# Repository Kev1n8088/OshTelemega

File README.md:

# Mega3080 v1.0

The Mega3080 FCU is an evolved clone of the Altus Metrum Telemega. Using the same firmware (meaning the same sensor suite), the primary developments are:
- USB-C
- Wago style spring terminals
- Better GPS RF routing, and external GPS antenna
- Companion port with extra UART and space for potential direct Mosaic Integration
- Mag switch with "hard to disarm" feature 
- Slightly smaller (30x80mm instead of 31.25x82.55mm)
- Better reverse polarity protection, including on pyro charges
- Cheaper than purchasing a TeleMega

## Basic Manual

All Wago ports are the same as the Telemega screw terminals, except for the addition of a connector to select between an external switch and the internal mag switch (you can use both!).

To enable the internal mag switch, bridge the terminals marked **MG**. A magnet's **N** pole perpendicular to the top surface magnetic sensor (under the square buzzer) arms the device. 

A fully armed device has the dual-LED next to the mag sensor fully lit (green and red). To begin the disarm process, expose the sensor to a **S** pole, then a **N** pole, and then an **S** pole. This will cycle the LED lights. This feature prevents any risk of disarming from launch towers that may generate magnetic fields.

If a device on the pad has a partially lit LED, the disarm process has started. It is recommended that a disarm and arming cycle be completed to reduce the risk of inadvertent disarm; however, even during the disarm process, the device remains as, if not less, sensitive to stray magnetic fields as industry-standard altimeters.

To use an external switch, simply wire it in series with the terminals marked **SW**. 

If you want an external switch in parallel with the internal mag switch **(NOT RECOMMENDED)** - you can wire both a switch in series with the **SW** terminals, and bridge the **MG** terminals. 

If you want an external switch in series with the internal mag switch **(MAYBE ALRIGHT?)** - you can wire a switch in series with the **MG** terminals. 

To enable GPS operation, connect a standard L1 patch antenna to the rear UFL connector marked L1 GPS. This port supports both passive and active patch antennas. 

Companion and servo connector documentation TBD

See the `flashing.md` file for flashing info. 

## Production
All SMT components can be assembled via JLCPCB.

THT BOM is to be produced soon. 

Use the `jlcpcb/production_files` subdirectory for production files. I do not guarantee that everything will be in stock on JLC, nor do I guarantee that the rotations are correct (they are not, **CHECK VERY CAREFULLY!**).

Recommended configuration is **JLC04161H-7628**. I recommend ENIG, but it's likely not necessary. 

## Notes
Use at your own risk! This device has not been validated as of Dec 2025, and custom production from JLC always carries the risk of QC issues. 

You must provide your own patch antenna (preferably active) to use the GPS

There are a few minor issues known with the v1.0 model: 

- When powered through the mag switch, there is a diode in the path for pyro power. This shouldn't be an issue in practice, but it is technically rated only for 1A continuous. The transient rating is more than enough at 50A, so it's not really a huge issue. There is also a slight voltage drop. Not an issue when the mag switch is bypassed or when a separate pyro battery is used.
- Theoretically, the vertical USB-C Connector is more fragile than a horizontal one - and also harder to solder with a hot air station. Take care when using heavy cables, and if you are concerned, epoxy the connector down.
- Due to a technical oversight, the separate pyro battery capability of the stock telemega, which is rated up to 30v, has to be derated to 12v on the Mega3080. Not sure how many people use a 12+v external pyro battery, but something to be aware of.

The v1.1 release has fixed the USB-C issue; however, the v1.1 device has not been produced yet. Use at your own risk.  

---

**Device Version Last Produced Officially:** v1.0

**Last Updated:** December 2025  

**Written by:** Kevin Zheng (Kev1n8088)

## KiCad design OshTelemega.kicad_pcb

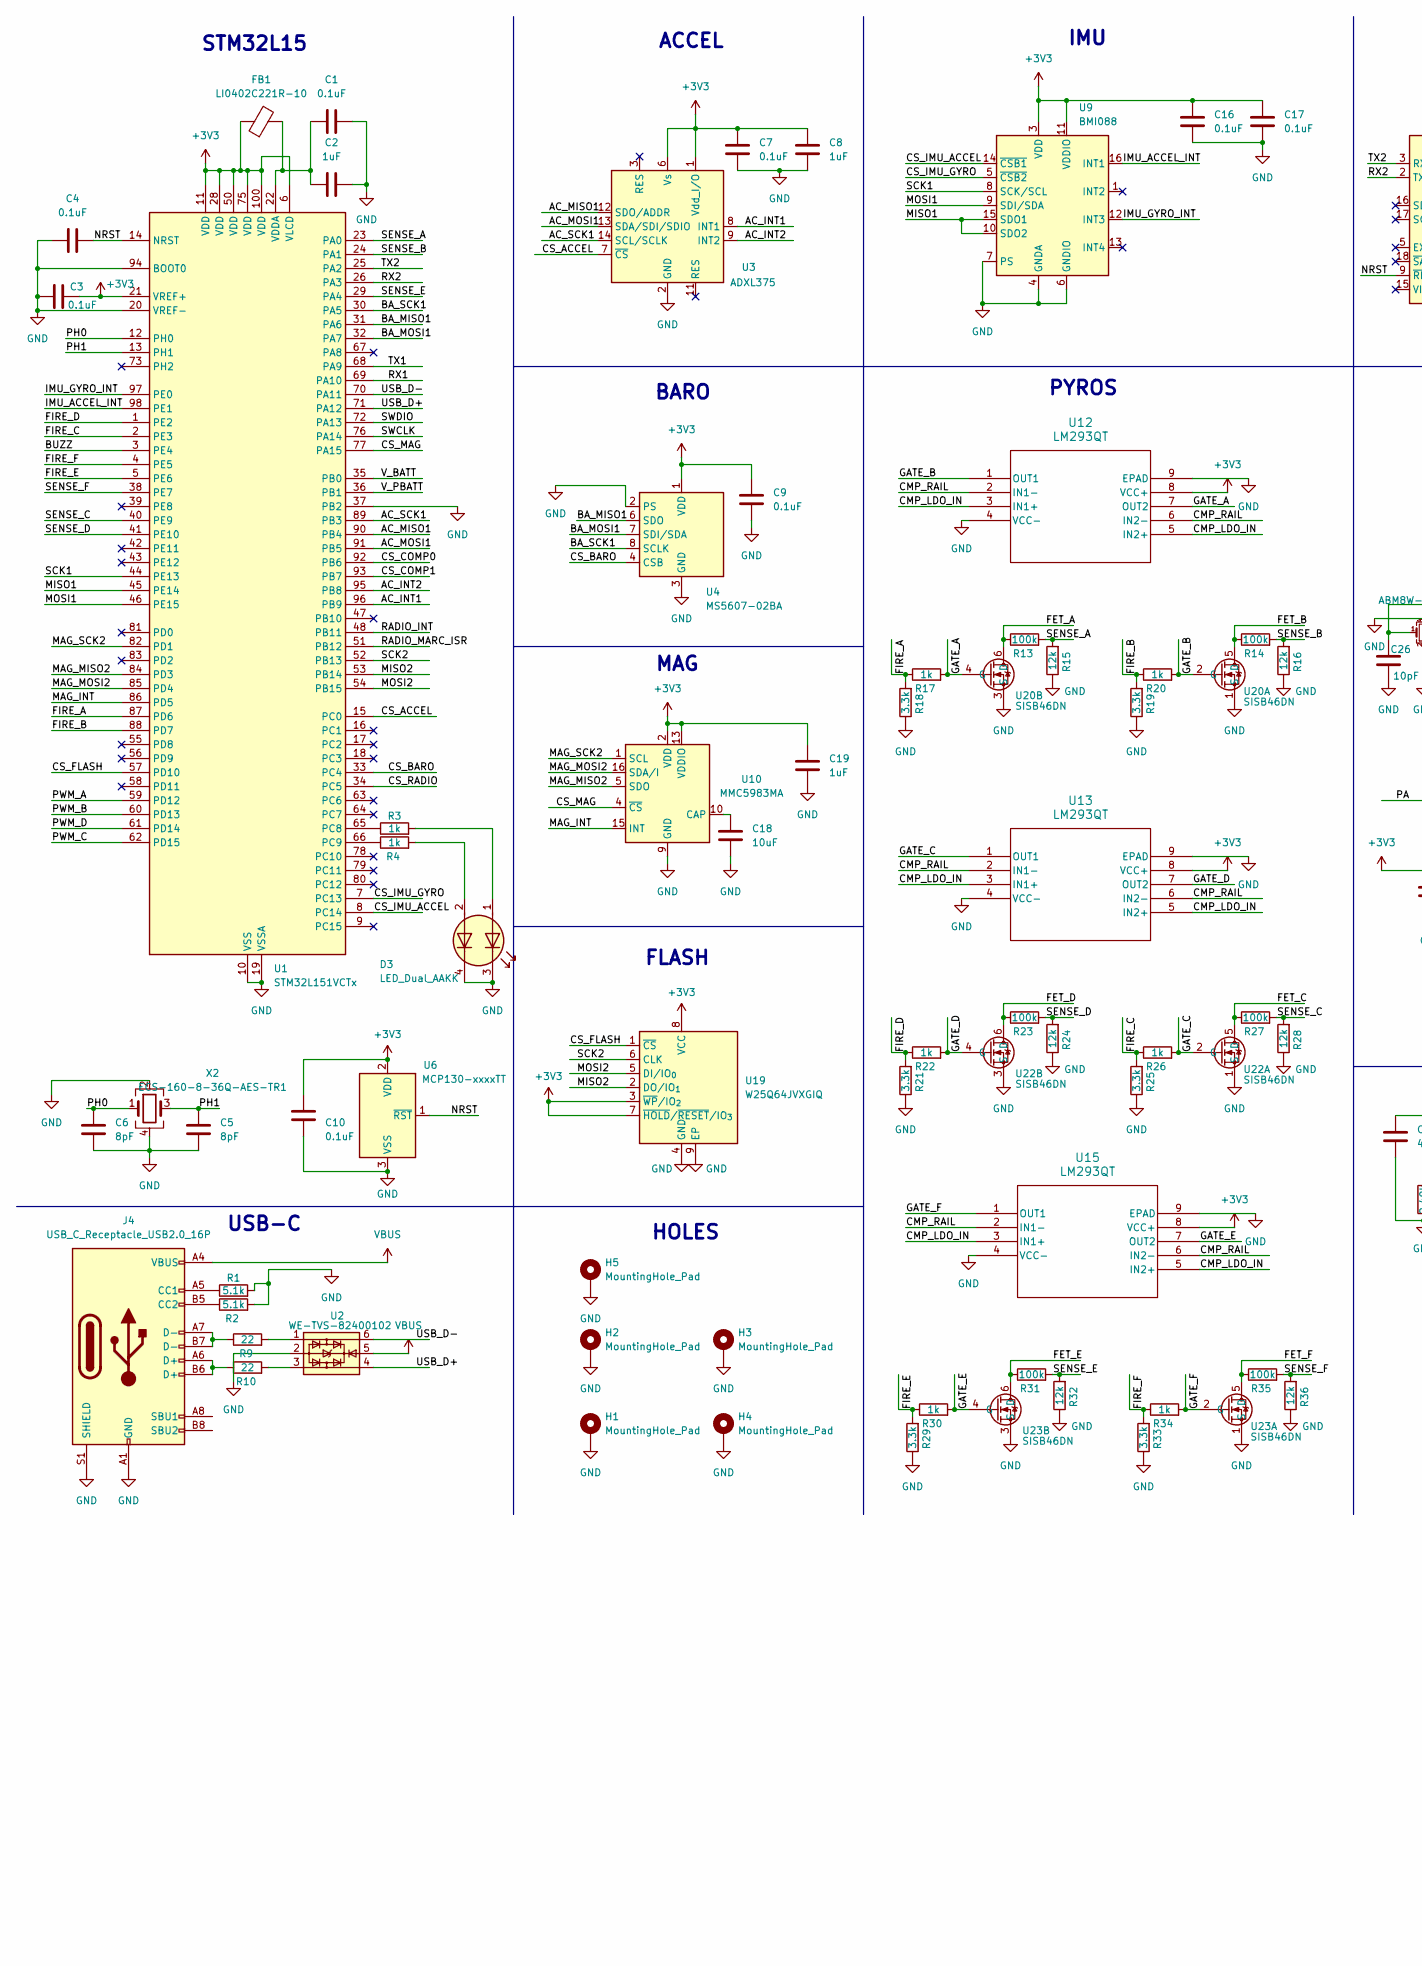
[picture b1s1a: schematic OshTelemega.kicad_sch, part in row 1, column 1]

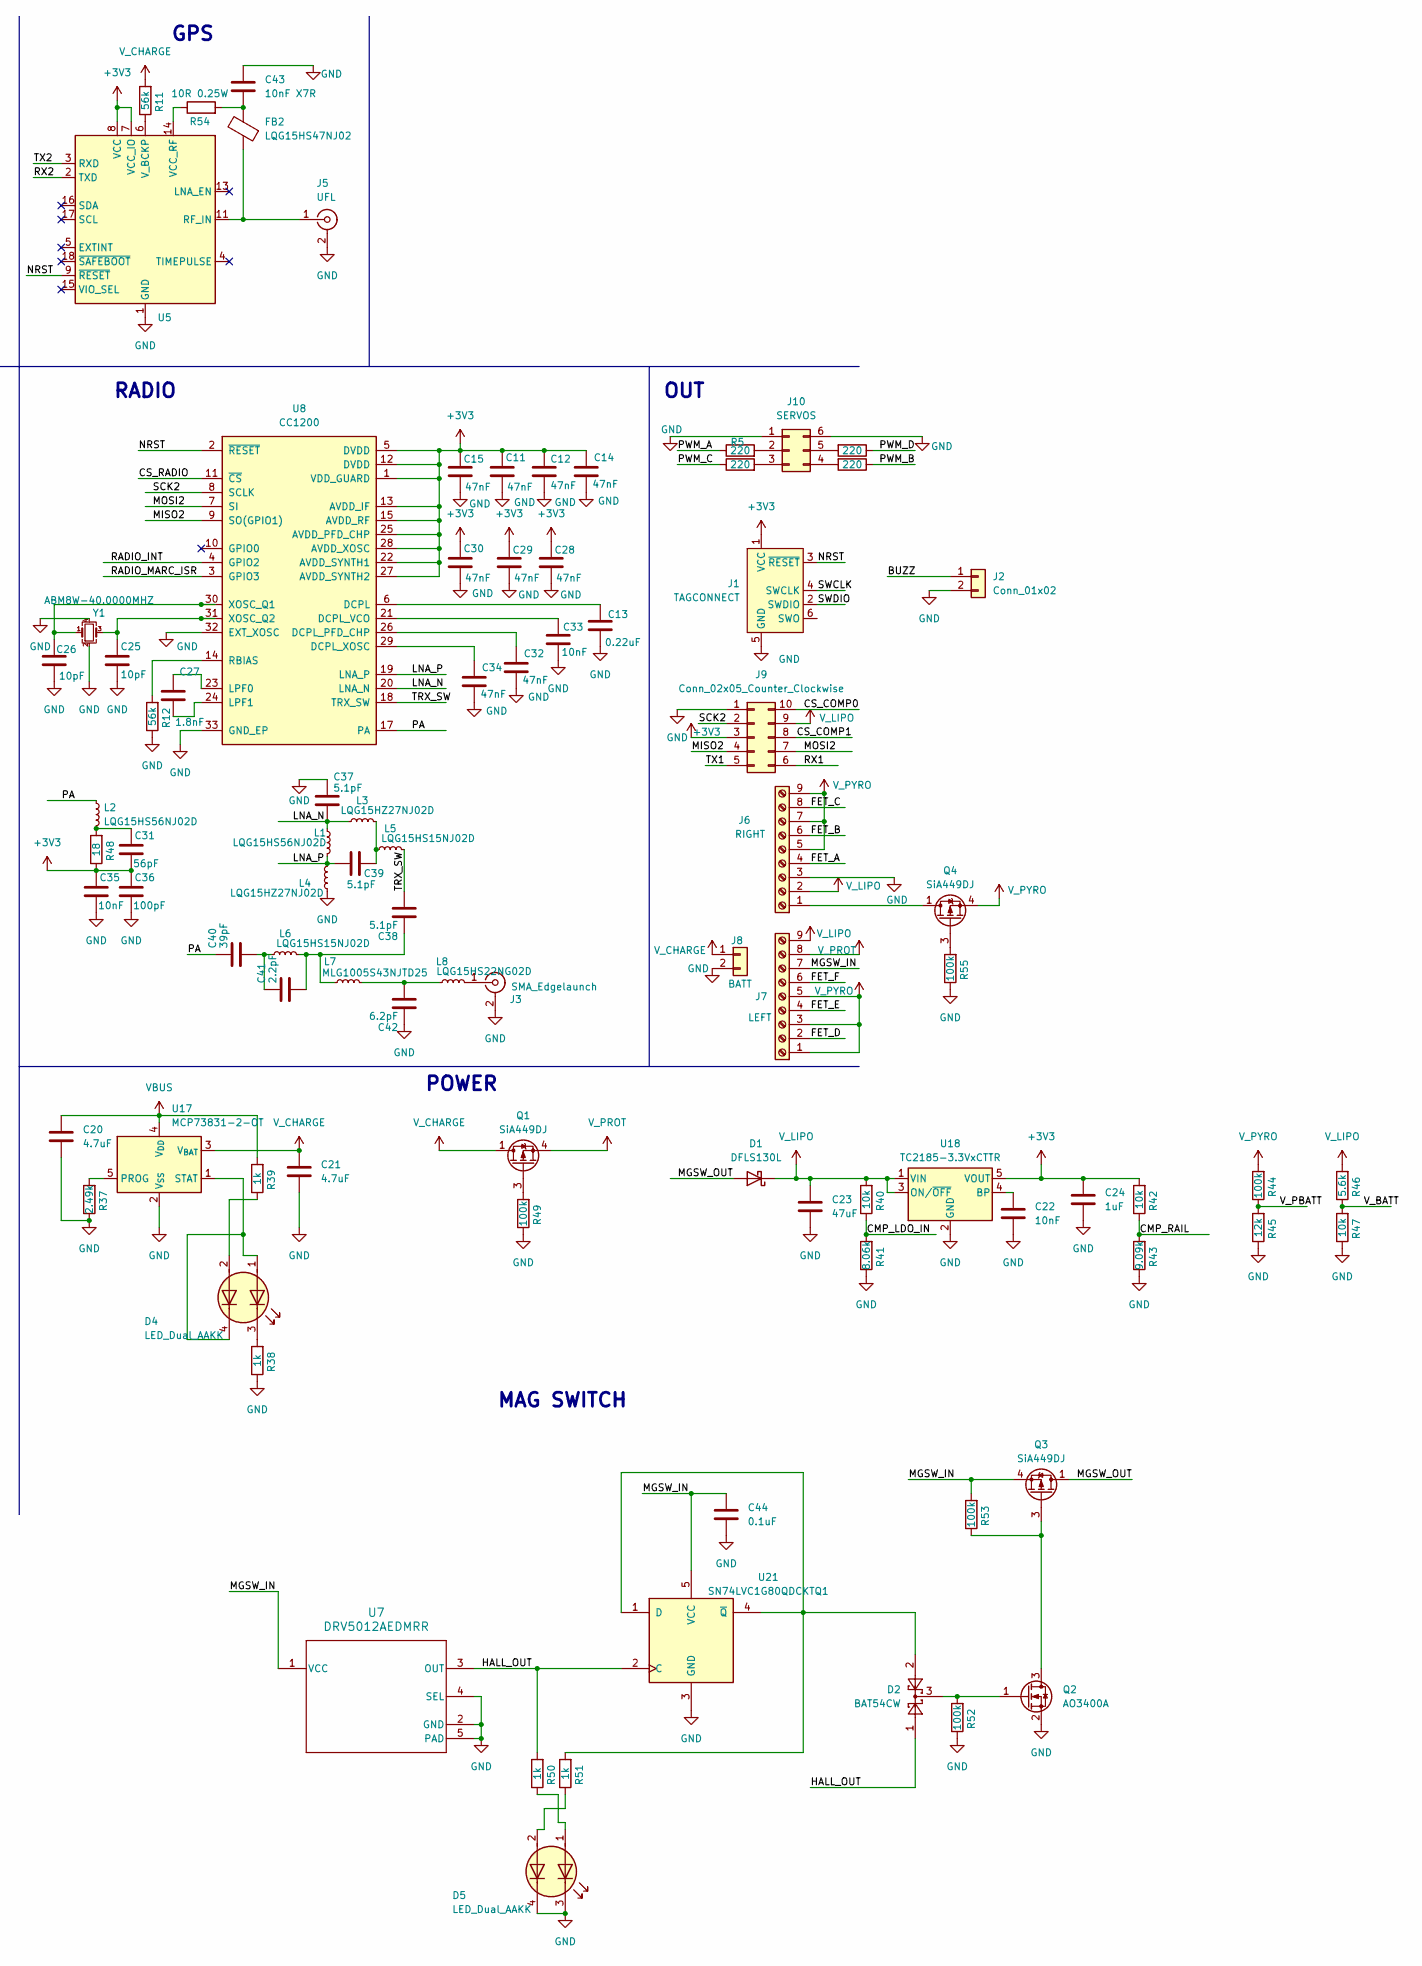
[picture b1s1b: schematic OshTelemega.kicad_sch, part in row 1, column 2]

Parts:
C1, C3, C4, C7, C9, C10, C16, C17, C44: 0.1uF; C_0402_1005Metric
C2, C8, C19, C24: 1uF; C_0402_1005Metric
C5, C6: 8pF; C_0402_1005Metric
C11, C12, C14, C15, C28, C29, C30, C32, C34: 47nF; C_0402_1005Metric
C13: 0.22uF; C_0402_1005Metric
C18: 10uF; C_0402_1005Metric
C20, C21: 4.7uF; C_0402_1005Metric
C22, C33, C35: 10nF; C_0402_1005Metric
C23: 47uF; C_1206_3216Metric
C25, C26: 10pF; C_0402_1005Metric
C27: 1.8nF; C_0402_1005Metric
C31: 56pF; C_0402_1005Metric
C36: 100pF; C_0402_1005Metric
C37, C38, C39: 5.1pF; C_0402_1005Metric
C40: 39pF; C_0402_1005Metric
C41: 2.2pF; C_0402_1005Metric
C42: 6.2pF; C_0402_1005Metric
C43: 10nF X7R; C_0402_1005Metric
D1: DFLS130L; D_PowerDI-123
D2: BAT54CW; SOT-323_SC-70
D3, D4, D5: LED_Dual_AAKK; DualLED0606
FB1: LI0402C221R-10; L_0402_1005Metric
FB2: LQG15HS47NJ02; L_0402_1005Metric
H1, H2, H3, H4, H5: MountingHole_Pad; MountingHole_3.2mm_M3_DIN965_Pad
J1: TAGCONNECT; Tag-Connect_TC2030-IDC-NL_2x03_P1.27mm_Vertical
J2: Conn_01x02; PinHeader_1x02_P1.27mm_Vertical
J3: SMA_Edgelaunch; SMA_Amphenol_132289_EdgeMount
J4: USB_C_Receptacle_USB2.0_16P; USB_C_Receptacle_G-Switch_GT-USB-7051x
J5: UFL; U.FL_Molex_MCRF_73412-0110_Vertical
J6: RIGHT; CONN9_250-309_WAG
J7: LEFT; CONN9_250-309_WAG
J8: BATT; JST_PH_B2B-PH-K_1x02_P2.00mm_Vertical
J9: Conn_02x05_Counter_Clockwise; PinHeader_2x05_P1.27mm_Vertical
J10: SERVOS; PinHeader_2x03_P1.27mm_Vertical
L1, L2: LQG15HS56NJ02D; L_0402_1005Metric
L3, L4: LQG15HZ27NJ02D; L_0402_1005Metric
L5, L6: LQG15HS15NJ02D; L_0402_1005Metric
L7: MLG1005S43NJTD25; L_0402_1005Metric
L8: LQG15HS22NG02D; L_0402_1005Metric
Q1, Q3, Q4: SiA449DJ; Vishay_PowerPAK_SC70-6L_Single
Q2: AO3400A; SOT-23
R1, R2: 5.1k; R_0402_1005Metric
R3, R4, R17, R20, R22, R26, R30, R34, R38, R39, R50, R51: 1k; R_0402_1005Metric
R5, R6, R7, R8: 220; R_0402_1005Metric
R9, R10: 22; R_0402_1005Metric
R11, R12: 56k; R_0402_1005Metric
R13, R14, R23, R27, R31, R35, R44, R49, R52, R53, R55: 100k; R_0402_1005Metric
R15, R16, R24, R28, R32, R36, R45: 12k; R_0402_1005Metric
R18, R19, R21, R25, R29, R33: 3.3k; R_0402_1005Metric
R37: 2.49k; R_0402_1005Metric
R40, R42, R47: 10k; R_0402_1005Metric
R41: 8.06k; R_0402_1005Metric
R43: 9.09k; R_0402_1005Metric
R46: 5.6k; R_0402_1005Metric
R48: 18; R_0402_1005Metric
R54: 10R 0.25W; R_0402_1005Metric
U1: STM32L151VCTx; LQFP-100_14x14mm_P0.5mm
U2: WE-TVS-82400102; SOT-23-6
U3: ADXL375; LGA-14_3x5mm_P0.8mm_LayoutBorder1x6y
U4: MS5607-02BA; LGA-8_3x5mm_P1.25mm
U5: MAX-M10S; ublox_MAX
U6: MCP130-xxxxTT; SOT-23
U7: DRV5012AEDMRR; Texas_X2SON-4-1EP_1.1x1.4mm_P0.5mm_EP0.8x0.6mm
U8: CC1200; QFN-32-1EP_5x5mm_P0.5mm_EP3.45x3.45mm
U9: BMI088; Bosch_LGA-16_4.5x3mm_P0.5mm_LayoutBorder7x1y_ClockwisePinNu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
U10: MMC5983MA; LGA-16_3x3mm_P0.5mm
U12, U13, U15: LM293QT; DFN-8-1EP_2x2mm_P0.5mm_EP0.9x1.6mm
U17: MCP73831-2-OT; SOT-23-5
U18: TC2185-3.3VxCTTR; SOT-23-5
U19: W25Q64JVXGIQ; DFN_XGIQ TR_WIN
U20, U22, U23: SISB46DN; PowerPak1212-8-Dual
U21: SN74LVC1G80QDCKTQ1; SOT-353_SC-70-5
X2: ECS-160-8-36Q-AES-TR1; Crystal_SMD_2520-4Pin_2.5x2.0mm
Y1: ABM8W-40.0000MHZ; Crystal_SMD_Abracon_ABM8G-4Pin_3.2x2.5mm

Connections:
+3V3: C3.2, C7.2, C8.2, C9.2, C10.2, C11.2, C12.2, C14.2, C15.2, C16.2, C17.2, C19.2, C24.2, C28.2, C29.2, C30.2, C31.1, C35.2, C36.2, FB1.1, J1.1 (VCC), J9.3, R42.2, R48.1, U1.6 (VLCD), U1.11 (VDD), U1.21 (VREF+), U1.28 (VDD), U1.50 (VDD), U1.75 (VDD), U1.100 (VDD), U3.1 (Vdd_I/O), U3.6 (Vs), U4.1 (VDD), U5.7 (VCC_IO), U5.8 (VCC), U6.2 (VDD), U8.1 (VDD_GUARD), U8.5 (DVDD), U8.12 (DVDD), U8.13 (AVDD_IF), U8.15 (AVDD_RF), U8.22 (AVDD_SYNTH1), U8.25 (AVDD_PFD_CHP), U8.27 (AVDD_SYNTH2), U8.28 (AVDD_XOSC), U9.3 (VDD), U9.11 (VDDIO), U10.2 (VDD), U10.13 (VDDIO), U12.8 (VCC+), U13.8 (VCC+), U15.8 (VCC+), U18.5 (VOUT), U19.3 (~WP/IO_{2}), U19.7 (~HOLD/~RESET/IO_{3}), U19.8 (VCC)
/AC_INT1: U1.96 (PB9), U3.8 (INT1)
/AC_INT2: U1.95 (PB8), U3.9 (INT2)
/AC_MISO1: U1.90 (PB4), U3.12 (SDO/ADDR)
/AC_MOSI1: U1.91 (PB5), U3.13 (SDA/SDI/SDIO)
/AC_SCK1: U1.89 (PB3), U3.14 (SCL/SCLK)
/BA_MISO1: U1.31 (PA6), U4.6 (SDO)
/BA_MOSI1: U1.32 (PA7), U4.7 (SDI/SDA)
/BA_SCK1: U1.30 (PA5), U4.8 (SCLK)
/BUZZ: J2.1, U1.3 (PE4); also elsewhere on the board
/CMP_LDO_IN: R40.1, R41.2, U12.3 (IN1+), U12.5 (IN2+), U13.3 (IN1+), U13.5 (IN2+), U15.3 (IN1+), U15.5 (IN2+)
/CMP_RAIL: R42.1, R43.2, U12.2 (IN1-), U12.6 (IN2-), U13.2 (IN1-), U13.6 (IN2-), U15.2 (IN1-), U15.6 (IN2-)
/CS_ACCEL: U1.15 (PC0), U3.7 (~CS)
/CS_BARO: U1.33 (PC4), U4.4 (CSB), U4.5 (CSB)
/CS_COMP0: J9.10, U1.92 (PB6)
/CS_COMP1: J9.8, U1.93 (PB7)
/CS_FLASH: U1.57 (PD10), U19.1 (~CS)
/CS_IMU_ACCEL: U1.8 (PC14), U9.14 (~CSB1)
/CS_IMU_GYRO: U1.7 (PC13), U9.5 (~CSB2)
/CS_MAG: U1.77 (PA15), U10.4 (~CS)
/CS_RADIO: U1.34 (PC5), U8.11 (~CS)
/FET_A: J6.4, R13.1, U20.6 (D)
/FET_B: J6.6, R14.1, U20.5 (D)
/FET_C: J6.8, R27.1, U22.5 (D)
/FET_D: J7.2, R23.1, U22.6 (D)
/FET_E: J7.4, R31.1, U23.6 (D)
/FET_F: J7.6, R35.1, U23.5 (D)
/FIRE_A: R17.1, R18.2, U1.87 (PD6)
/FIRE_B: R19.2, R20.1, U1.88 (PD7)
/FIRE_C: R25.2, R26.1, U1.2 (PE3)
/FIRE_D: R21.2, R22.1, U1.1 (PE2)
/FIRE_E: R29.2, R30.1, U1.5 (PE6)
/FIRE_F: R33.2, R34.1, U1.4 (PE5)
/GATE_A: R17.2, U12.7 (OUT2), U20.4 (G)
/GATE_B: R20.2, U12.1 (OUT1), U20.2 (G)
/GATE_C: R26.2, U13.1 (OUT1), U22.2 (G)
/GATE_D: R22.2, U13.7 (OUT2), U22.4 (G)
/GATE_E: R30.2, U15.7 (OUT2), U23.4 (G)
/GATE_F: R34.2, U15.1 (OUT1), U23.2 (G)
/HALL_OUT: D2.1, R50.2, U7.3 (OUT), U21.2 (C)
/IMU_ACCEL_INT: U1.98 (PE1), U9.16 (INT1)
/IMU_GYRO_INT: U1.97 (PE0), U9.12 (INT3)
/LNA_N: C37.1, L1.1, L3.1, U8.20 (LNA_N)
/LNA_P: C39.2, L1.2, L4.2, U8.19 (LNA_P)
/MAG_INT: U1.86 (PD5), U10.15 (INT)
/MAG_MISO2: U1.84 (PD3), U10.5 (SDO)
/MAG_MOSI2: U1.85 (PD4), U10.16 (SDA/I)
/MAG_SCK2: U1.82 (PD1), U10.1 (SCL)
/MGSW_IN: C44.2, J7.7, Q3.4 (S), R53.2, U7.1 (VCC), U21.5 (VCC)
/MGSW_OUT: D1.2 (A), Q3.1 (D)
/MISO1: U1.45 (PE14), U9.10 (SDO2), U9.15 (SDO1)
/MISO2: J9.4, U1.53 (PB14), U8.9 (SO(GPIO1)), U19.2 (DO/IO_{1})
/MOSI1: U1.46 (PE15), U9.9 (SDI/SDA)
/MOSI2: J9.7, U1.54 (PB15), U8.7 (SI), U19.5 (DI/IO_{0})
/NRST: C4.2, J1.3 (~RESET), U1.14 (NRST), U5.9 (~RESET), U6.1 (~RST), U8.2 (~RESET)
/PA: C40.2, L2.1, U8.17 (PA)
/PH0: C6.2, U1.12 (PH0), X2.1
/PH1: C5.2, U1.13 (PH1), X2.3
/PWM_A: R5.1, U1.59 (PD12)
/PWM_B: R6.1, U1.60 (PD13)
/PWM_C: R7.1, U1.62 (PD15)
/PWM_D: R8.1, U1.61 (PD14)
/RADIO_INT: U1.48 (PB11), U8.4 (GPIO2)
/RADIO_MARC_ISR: U1.51 (PB12), U8.3 (GPIO3)
/RX1: J9.6, U1.69 (PA10)
/RX2: U1.26 (PA3), U5.2 (TXD)
/SCK1: U1.44 (PE13), U9.8 (SCK/SCL)
/SCK2: J9.2, U1.52 (PB13), U8.8 (SCLK), U19.6 (CLK)
/SENSE_A: R13.2, R15.2, U1.23 (PA0)
/SENSE_B: R14.2, R16.2, U1.24 (PA1)
/SENSE_C: R27.2, R28.2, U1.40 (PE9)
/SENSE_D: R23.2, R24.2, U1.41 (PE10)
/SENSE_E: R31.2, R32.2, U1.29 (PA4)
/SENSE_F: R35.2, R36.2, U1.38 (PE7)
/SWCLK: J1.4 (SWCLK), U1.76 (PA14)
/SWDIO: J1.2 (SWDIO), U1.72 (PA13)
/TRX_SW: C38.1, L5.2, U8.18 (TRX_SW)
/TX1: J9.5, U1.68 (PA9)
/TX2: U1.25 (PA2), U5.3 (RXD)
/USB_D+: U1.71 (PA12), U2.4
/USB_D-: U1.70 (PA11), U2.6
/V_BATT: R46.1, R47.2, U1.35 (PB0)
/V_PBATT: R44.1, R45.2, U1.36 (PB1)
GND: C1.2, C2.2, C3.1, C4.1, C5.1, C6.1, C7.1, C8.1, C9.1, C10.1, C11.1, C12.1, C13.1, C14.1, C15.1, C16.1, C17.1, C18.1, C19.1, C20.1, C21.1, C22.1, C23.1, C24.1, C25.1, C26.1, C28.1, C29.1, C30.1, C32.1, C33.1, C34.1, C35.1, C36.1, C37.2, C42.2, C43.2, C44.1, D3.3 (K1), D3.4 (K2), D5.3 (K1), D5.4 (K2), H1.1, H2.1, H3.1, H4.1, H5.1, J1.5 (GND), J2.2, J3.2 (Ext), J4.A1 (GND), J4.A12 (GND), J4.B1 (GND), J4.B12 (GND), J4.S1 (SHIELD), J5.2 (Ext), J6.3, J8.2, J9.1, J10.1, J10.6, L4.1, Q2.2 (S), R1.2, R2.2, R12.1, R15.1, R16.1, R18.1, R19.1, R21.1, R24.1, R25.1, R28.1, R29.1, R32.1, R33.1, R36.1, R37.1, R38.1, R41.1, R43.1, R45.1, R47.1, R49.1, R52.1, R55.1, U1.10 (VSS), U1.19 (VSSA), U1.20 (VREF-), U1.27 (VSS), U1.37 (PB2), U1.49 (VSS), U1.74 (VSS), U1.94 (BOOT0), U1.99 (VSS), U2.2, U3.2 (GND), U3.4 (GND), U3.5 (GND), U4.2 (PS), U4.3 (GND), U5.1 (GND), U5.10 (GND), U5.12 (GND), U6.3 (VSS), U7.2 (GND), U7.4 (SEL), U7.5 (PAD), U8.32 (EXT_XOSC), U8.33 (GND_EP), U9.2 (GNDA), U9.4 (GNDA), U9.6 (GNDIO), U9.7 (PS), U10.9 (GND), U10.11 (GND), U12.4 (VCC-), U12.9 (EPAD), U13.4 (VCC-), U13.9 (EPAD), U15.4 (VCC-), U15.9 (EPAD), U17.2 (V_{SS}), U18.2 (GND), U19.4 (GND), U19.9 (EP), U20.1 (S), U20.3 (S), U21.3 (GND), U22.1 (S), U22.3 (S), U23.1 (S), U23.3 (S), X2.2, X2.4, Y1.2, Y1.4; also elsewhere on the board
unnamed: C31.2, L2.2, R48.2
unnamed: C38.2, C41.1, L6.2, L7.1
unnamed: C39.1, L3.2, L5.1
unnamed: C40.1, C41.2, L6.1
unnamed: C42.1, L7.2, L8.1
unnamed: C43.1, FB2.2, R54.2
unnamed: D3.1 (A1), R3.2
unnamed: D3.2 (A2), R4.2
unnamed: D4.1 (A1), D4.4 (K2), U17.1 (STAT)
unnamed: D4.2 (A2), R39.1
unnamed: D4.3 (K1), R38.2
unnamed: D5.1 (A1), R50.1
unnamed: D5.2 (A2), R51.1
unnamed 97: U5.4 (TIMEPULSE); also elsewhere on the board
unnamed: J3.1 (In), L8.2
unnamed: J4.A5 (CC1), R1.1
unnamed: J4.B5 (CC2), R2.1
unnamed: J4.A6 (D+), J4.B6 (D+), R10.1
unnamed: J4.A7 (D-), J4.B7 (D-), R9.1
unnamed: FB2.1, J5.1 (In), U5.11 (RF_IN)
unnamed: J6.1, Q4.1 (D)
unnamed: J10.2, R5.2
unnamed: J10.3, R7.2
unnamed: J10.4, R6.2
unnamed: J10.5, R8.2
unnamed: Q1.3 (G), R49.2
unnamed: Q2.3 (D), Q3.3 (G), R53.1
unnamed: D2.3, Q2.1 (G), R52.2
unnamed: Q4.3 (G), R55.2
unnamed: R9.2, U2.1
unnamed: R10.2, U2.3
unnamed: R3.1, U1.65 (PC8)
unnamed: R4.1, U1.66 (PC9)
unnamed: C1.1, C2.1, FB1.2, U1.22 (VDDA)
unnamed: R54.1, U5.14 (VCC_RF)
unnamed: R11.1, U5.6 (V_BCKP)
unnamed: C13.2, U8.6 (DCPL)
unnamed: C32.2, U8.26 (DCPL_PFD_CHP)
unnamed: C33.2, U8.21 (DCPL_VCO)
unnamed: C34.2, U8.29 (DCPL_XOSC)
unnamed: C27.2, U8.23 (LPF0)
unnamed: C27.1, U8.24 (LPF1)
unnamed: R12.2, U8.14 (RBIAS)
unnamed: C26.2, U8.30 (XOSC_Q1), Y1.1
unnamed: C25.2, U8.31 (XOSC_Q2), Y1.3
unnamed: C18.2, U10.10 (CAP)
unnamed: R37.2, U17.5 (PROG)
unnamed: C22.2, U18.4 (BP)
unnamed: D2.2, R51.2, U21.1 (D), U21.4 (~Q)
VBUS: C20.2, J4.A4 (VBUS), J4.A9 (VBUS), J4.B4 (VBUS), J4.B9 (VBUS), R39.2, U2.5, U17.4 (V_{DD})
V_CHARGE: C21.2, J8.1, Q1.1 (D), R11.2, U17.3 (V_{BAT})
V_LIPO: C23.2, D1.1 (K), J6.2, J7.9, J9.9, R40.2, R46.2, U18.1 (VIN), U18.3 (ON/~OFF)
V_PROT: J7.8, Q1.4 (S)
V_PYRO: J6.5, J6.7, J6.9, J7.1, J7.3, J7.5, Q4.4 (S), R44.2

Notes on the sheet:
HOLES
MAG SWITCH
BARO
STM32L15
USB-C
MAG
ACCEL
GPS
RADIO
IMU
PYROS
OUT
FLASH
POWER

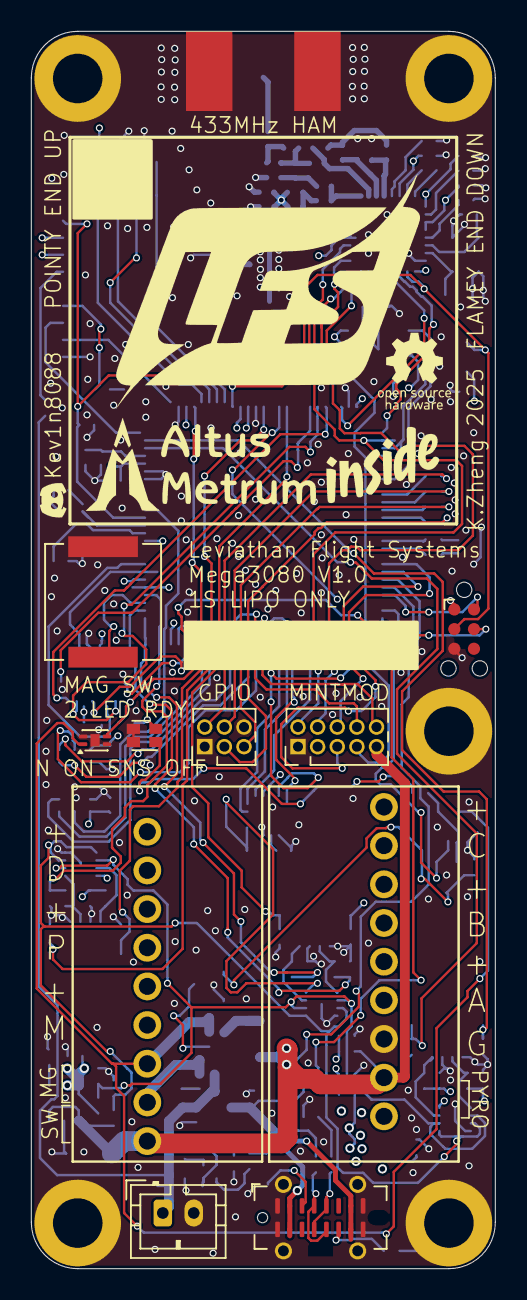
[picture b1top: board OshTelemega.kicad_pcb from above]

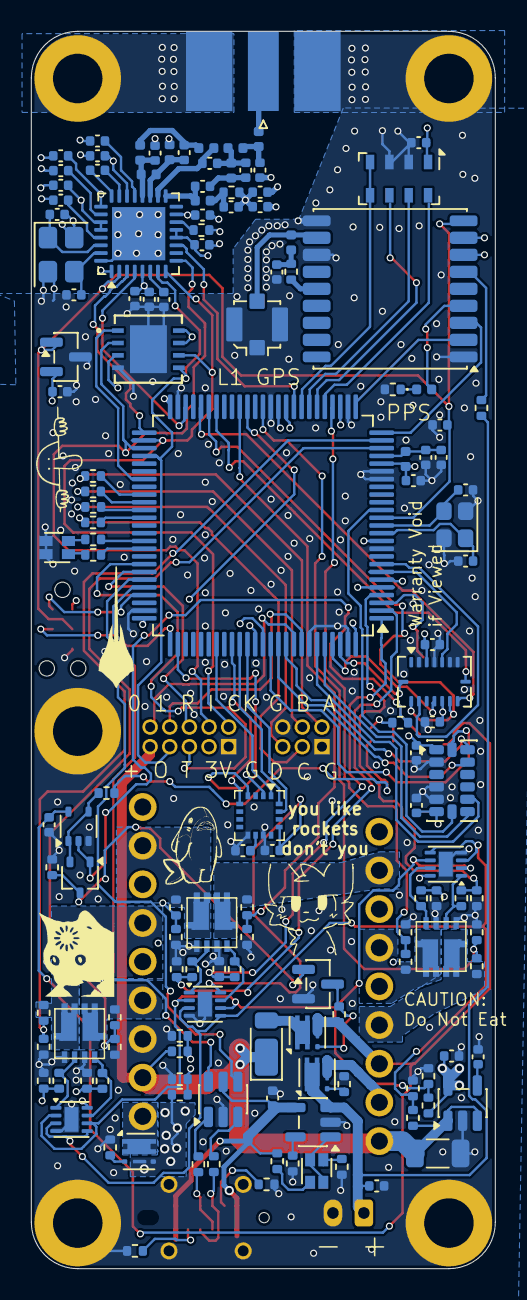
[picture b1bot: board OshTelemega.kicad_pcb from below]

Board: 4 copper layers, 30.0 x 80.0 mm, 157 parts (142 on the bottom side), 139 nets.

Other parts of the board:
D6: PPS; LED_0402_1005Metric
R56: 1k; R_0402_1005Metric
U11: CPE-171; XDCR_CPT-7502-65-SMT-TR

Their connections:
/BUZZ: U11.P; also elsewhere on the board
GND: R56.2, U11.N; also elsewhere on the board
unnamed 97: D6.2 (A); also elsewhere on the board
unnamed: D6.1 (K), R56.1

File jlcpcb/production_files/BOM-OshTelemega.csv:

Comment,Designator,Footprint,LCSC,Quantity
1.8nF,C27,C_0402_1005Metric,C107024,1
DFLS130L,D1,D_PowerDI-123,C110493,1
56k,"R11,R12",R_0402_1005Metric,C114756,2
1k,"R17,R20,R22,R26,R3,R30,R34,R38,R39,R4,R50,R51,R56",R_0402_1005Metric,C11702,13
CC1200,U8,QFN-32-1EP_5x5mm_P0.5mm_EP3.45x3.45mm,C122881,1
LQG15HS22NG02D,L8,L_0402_1005Metric,C12670,1
STM32L151VCTx,U1,LQFP-100_14x14mm_P0.5mm,C1338621,1
5.6k,R46,R_0402_1005Metric,C137856,1
2.49k,R37,R_0402_1005Metric,C145071,1
MCP73831-2-OT,U17,SOT-23-5,C14879,1
10nF,"C22,C33,C35,C43",C_0402_1005Metric,C15195,4
0.1uF,"C1,C10,C16,C17,C3,C4,C44,C7,C9",C_0402_1005Metric,C1525,9
100pF,C36,C_0402_1005Metric,C1546,1
8pF,"C5,C6",C_0402_1005Metric,C1549,2
10uF,C18,C_0402_1005Metric,C15525,1
6.2pF,C42,C_0402_1005Metric,C161332,1
56pF,C31,C_0402_1005Metric,C162113,1
LQG15HS56NJ02D,"L1,L2",L_0402_1005Metric,C162544,2
ECS-160-8-36Q-AES-TR1,X2,Crystal_SMD_2520-4Pin_2.5x2.0mm,C1669787,1
0.22uF,C13,C_0402_1005Metric,C16772,1
LED_Dual_AAKK,"D3,D4,D5",DualLED0606,C183840,3
BMI088,U9,Bosch_LGA-16_4.5x3mm_P0.5mm_LayoutBorder7x1y_ClockwisePinNumbering,C194919,1
WE-TVS-82400102,U2,SOT-23-6,C1975330,1
MLG1005S43NJTD25,L7,L_0402_1005Metric,C2042359,1
AO3400A,Q2,SOT-23,C20917,1
SISB46DN,"U20,U22,U23",PowerPak1212-8-Dual,C22366987,3
8.06k,R41,R_0402_1005Metric,C227258,1
4.7uF,"C20,C21",C_0402_1005Metric,C23733,2
10R 0.25W,R54,R_0402_1005Metric,C25077,1
18,R48,R_0402_1005Metric,C25084,1
220,"R5,R6,R7,R8",R_0402_1005Metric,C25091,4
22,"R10,R9",R_0402_1005Metric,C25092,2
ABM8W-40.0000MHZ,Y1,Crystal_SMD_Abracon_ABM8G-4Pin_3.2x2.5mm,C255943,1
100k,"R13,R14,R23,R27,R31,R35,R44,R49,R52,R53",R_0402_1005Metric,C25741,10
10k,"R40,R42,R47",R_0402_1005Metric,C25744,3
12k,"R15,R16,R24,R28,R32,R36,R45",R_0402_1005Metric,C25752,7
3.3k,"R18,R19,R21,R25,R29,R33",R_0402_1005Metric,C25890,6
5.1k,"R1,R2",R_0402_1005Metric,C25905,2
LI0402C221R-10,FB1,L_0402_1005Metric,C269768,1
9.09k,R43,R_0402_1005Metric,C274897,1
UFL,J5,U.FL_Molex_MCRF_73412-0110_Vertical,C277719,1
TC2185-3.3VxCTTR,U18,SOT-23-5,C2798212,1
5.1pF,"C37,C38,C39",C_0402_1005Metric,C281761,3
W25Q64JVXGIQ,U19,DFN_XGIQ TR_WIN,C2940195,1
LM293QT,"U12,U13,U15",DFN-8-1EP_2x2mm_P0.5mm_EP0.9x1.6mm,C2970217,3
39pF,C40,C_0402_1005Metric,C327068,1
10pF,"C25,C26",C_0402_1005Metric,C32949,2
PPS,D6,LED_0402_1005Metric,C364550,1
MMC5983MA,U10,LGA-16_3x3mm_P0.5mm,C404329,1
MAX-M10S,U5,ublox_MAX,C4153167,1
SN74LVC1G80QDCKTQ1,U21,SOT-353_SC-70-5,C473331,1
ADXL375,U3,LGA-14_3x5mm_P0.8mm_LayoutBorder1x6y,C481898,1
1uF,"C19,C2,C24,C8",C_0402_1005Metric,C52923,4
LQG15HZ27NJ02D,"L3,L4",L_0402_1005Metric,C560069,2
47nF,"C11,C12,C14,C15,C28,C29,C30,C32,C34",C_0402_1005Metric,C576715,9
100k,R55,R_0402_1005Metric,C60491,1
MCP130-xxxxTT,U6,SOT-23,C625194,1
SiA449DJ,"Q1,Q3,Q4",Vishay_PowerPAK_SC70-6L_Single,C727325,3
BAT54CW,D2,SOT-323_SC-70,C82467,1
LQG15HS15NJ02D,"L5,L6",L_0402_1005Metric,C86059,2
2.2pF,C41,C_0402_1005Metric,C88887,1
47uF,C23,C_1206_3216Metric,C96123,1
MS5607-02BA,U4,LGA-8_3x5mm_P1.25mm,C97627,1
LQG15HS47NJ02,FB2,L_0402_1005Metric,C97998,1
DRV5012AEDMRR,U7,Texas_X2SON-4-1EP_1.1x1.4mm_P0.5mm_EP0.8x0.6mm,,1
RIGHT,J6,CONN9_250-309_WAG,,1
BATT,J8,JST_PH_B2B-PH-K_1x02_P2.00mm_Vertical,,1
USB_C_Receptacle_USB2.0_16P,J4,USB_C_Receptacle_G-Switch_GT-USB-7051x,,1
Conn_02x05_Counter_Clockwise,J9,PinHeader_2x05_P1.27mm_Vertical,,1
SERVOS,J10,PinHeader_2x03_P1.27mm_Vertical,,1
LEFT,J7,CONN9_250-309_WAG,,1
SMA_Edgelaunch,J3,SMA_Amphenol_132289_EdgeMount,,1
CPE-171,U11,XDCR_CPT-7502-65-SMT-TR,,1

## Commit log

2025-10-08 v0.1 done. Redesigning for potential mosaic integration
2025-10-09 before adding 10 pin companion
2025-10-09 v0.2 done - just needs review and silkscreens
2025-10-09 removed backup zips
2025-10-09 added gitignore
2025-10-09 some jlc manufacturing considerations
2025-10-09 fixed wrong orientation on mag switch mosfet
2025-10-09 added pyro rp protection
2025-10-10 expanded SMA connector and added some more silkscreens
2025-10-11 finished silkscreen edits. Switching branches to work on JLC DRC
2025-10-11 drc changes and more ground stitching
2025-10-11 minor impedance tune due to new pour clearance
2025-10-13 minor changes
2025-10-13 changes to vias and silkscreens
2025-10-13 resolved drc, added buzzer, and PPS led
2025-10-13 silkscreen memes
2025-10-14 tunes for production run 1
2025-10-20 minor prod updates
2025-11-17 v1.0 production variant
2025-12-03 Add README for Mega3080 FCU v1.0
    Added detailed documentation for the Mega3080 FCU, including features, usage instructions, production notes, and known issues.
2025-12-03 Added flashing readme
2025-12-03 Fix grammar and clarity issues in README.md
    Corrected minor grammatical errors and improved clarity in the README.
